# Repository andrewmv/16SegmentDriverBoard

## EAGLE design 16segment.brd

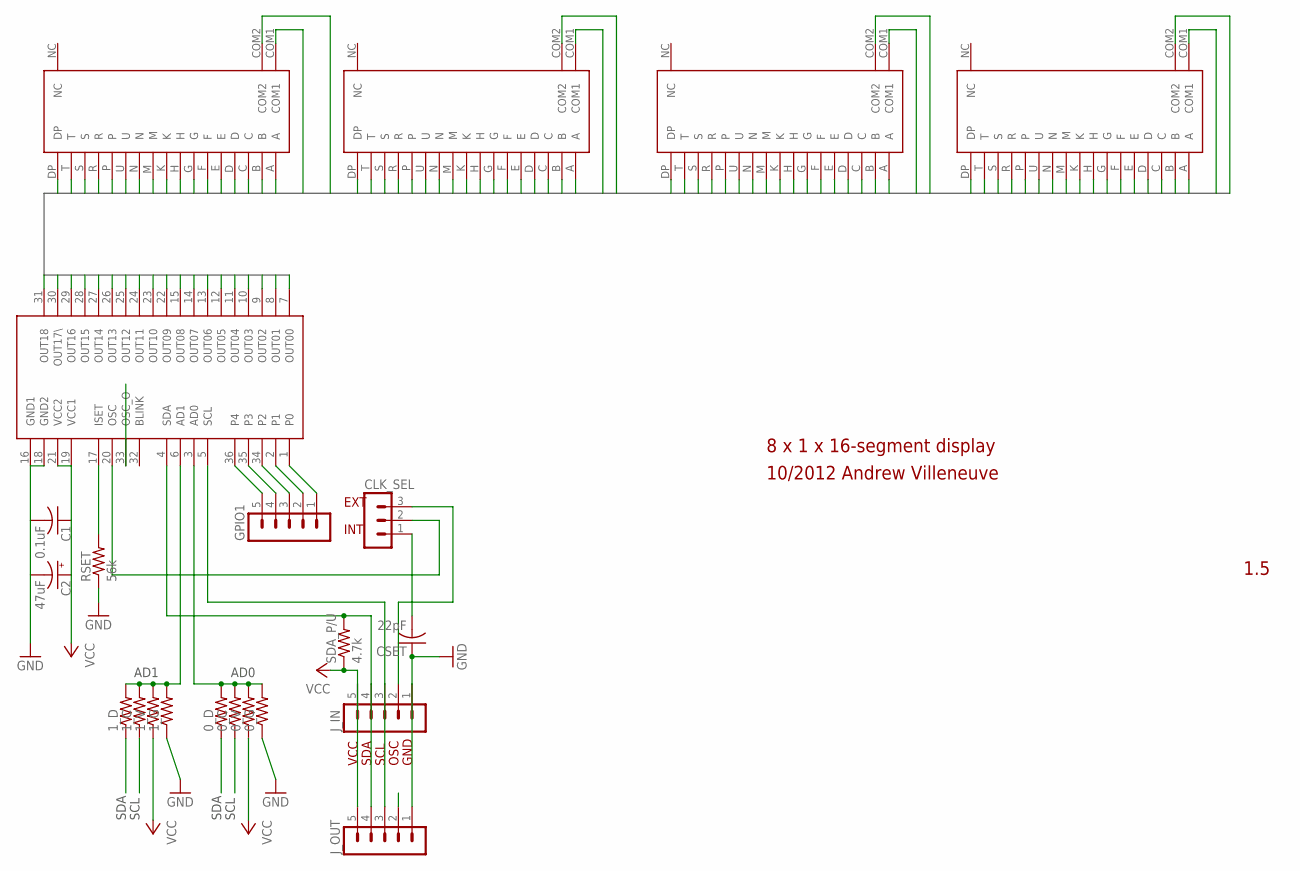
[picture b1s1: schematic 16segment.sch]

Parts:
0_C, 0_D, 0_G, 0_V, 1_C, 1_D, 1_G, 1_V: R-US_R0805; R0805
C1: 0.1uF; C0805
C2: 47uF; E2,5-6
CLK_SEL: MA03-1
CSET: 22pF; C0805
DIGIT0,1, DIGIT2,3, DIGIT4,5, DIGIT6,7: LTP-4323JD
GPIO1: MA05-1
IC1: MAX6955; SSOP36
J_IN: MA05-1
J_OUT: MA05-1
RSET: 56k; R0805
SDA_P/U: 4.7k; R0805

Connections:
AD0: 0_C.2, 0_D.2, 0_G.2, 0_V.2, IC1.3 (AD0)
AD1: 1_C.2, 1_D.2, 1_G.2, 1_V.2, IC1.6 (AD1)
EXT_OSC_IN: CLK_SEL.3, J_IN.2
GND: 0_G.1, 1_G.1, C1.2, C2.-, CSET.1, IC1.16 (GND1), IC1.18 (GND2), J_IN.1, J_OUT.1, RSET.1
GPIO_0: GPIO1.1, IC1.1 (P0)
GPIO_1: GPIO1.2, IC1.2 (P1)
GPIO_2: GPIO1.3, IC1.34 (P2)
GPIO_3: GPIO1.4, IC1.35 (P3)
GPIO_4: GPIO1.5, IC1.36 (P4)
IC1_OSC: CLK_SEL.2, IC1.20 (OSC)
INT_OSC: CLK_SEL.1, CSET.2
ISET: IC1.17 (ISET), RSET.2
OSC_O: IC1.33 (OSC_O), J_OUT.2
OUT0: DIGIT0,1.COM1, DIGIT2,3.A, DIGIT4,5.A, DIGIT6,7.A, IC1.7 (OUT00)
OUT1: DIGIT0,1.COM2, DIGIT2,3.B, DIGIT4,5.B, DIGIT6,7.B, IC1.8 (OUT01)
OUT2: DIGIT0,1.A, DIGIT2,3.COM1, DIGIT4,5.C, DIGIT6,7.C, IC1.9 (OUT02)
OUT3: DIGIT0,1.B, DIGIT2,3.COM2, DIGIT4,5.D, DIGIT6,7.D, IC1.10 (OUT03)
OUT4: DIGIT0,1.C, DIGIT2,3.C, DIGIT4,5.COM1, DIGIT6,7.E, IC1.11 (OUT04)
OUT5: DIGIT0,1.D, DIGIT2,3.D, DIGIT4,5.COM2, DIGIT6,7.F, IC1.12 (OUT05)
OUT6: DIGIT0,1.E, DIGIT2,3.E, DIGIT4,5.E, DIGIT6,7.COM1, IC1.13 (OUT06)
OUT7: DIGIT0,1.F, DIGIT2,3.F, DIGIT4,5.F, DIGIT6,7.COM2, IC1.14 (OUT07)
OUT8: DIGIT0,1.G, DIGIT2,3.G, DIGIT4,5.G, DIGIT6,7.G, IC1.15 (OUT08)
OUT9: DIGIT0,1.H, DIGIT2,3.H, DIGIT4,5.H, DIGIT6,7.H, IC1.22 (OUT09)
OUT10: DIGIT0,1.U, DIGIT2,3.U, DIGIT4,5.U, DIGIT6,7.U, IC1.23 (OUT10)
OUT11: DIGIT0,1.P, DIGIT2,3.P, DIGIT4,5.P, DIGIT6,7.P, IC1.24 (OUT11)
OUT12: DIGIT0,1.K, DIGIT2,3.K, DIGIT4,5.K, DIGIT6,7.K, IC1.25 (OUT12)
OUT13: DIGIT0,1.M, DIGIT2,3.M, DIGIT4,5.M, DIGIT6,7.M, IC1.26 (OUT13)
OUT14: DIGIT0,1.N, DIGIT2,3.N, DIGIT4,5.N, DIGIT6,7.N, IC1.27 (OUT14)
OUT15: DIGIT0,1.R, DIGIT2,3.R, DIGIT4,5.R, DIGIT6,7.R, IC1.28 (OUT15)
OUT16: DIGIT0,1.S, DIGIT2,3.S, DIGIT4,5.S, DIGIT6,7.S, IC1.29 (OUT16)
OUT17: DIGIT0,1.T, DIGIT2,3.T, DIGIT4,5.T, DIGIT6,7.T, IC1.30 (OUT17\)
OUT18: DIGIT0,1.DP, DIGIT2,3.DP, DIGIT4,5.DP, DIGIT6,7.DP, IC1.31 (OUT18)
SCL: 0_C.1, 1_C.1, IC1.5 (SCL), J_IN.3, J_OUT.3
SDA: IC1.4 (SDA), J_IN.4, J_OUT.4, SDA_P/U.2
SDA_0: 0_D.1, 1_D.1
VCC: 0_V.1, 1_V.1, C1.1, C2.+, IC1.19 (VCC1), IC1.21 (VCC2), J_IN.5, J_OUT.5, SDA_P/U.1

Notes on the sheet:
8 x 1 x 16-segment display
1.5
10/2012 Andrew Villeneuve
VCC
SDA
SCL
OSC
GND
INT
EXT
AD0
AD1

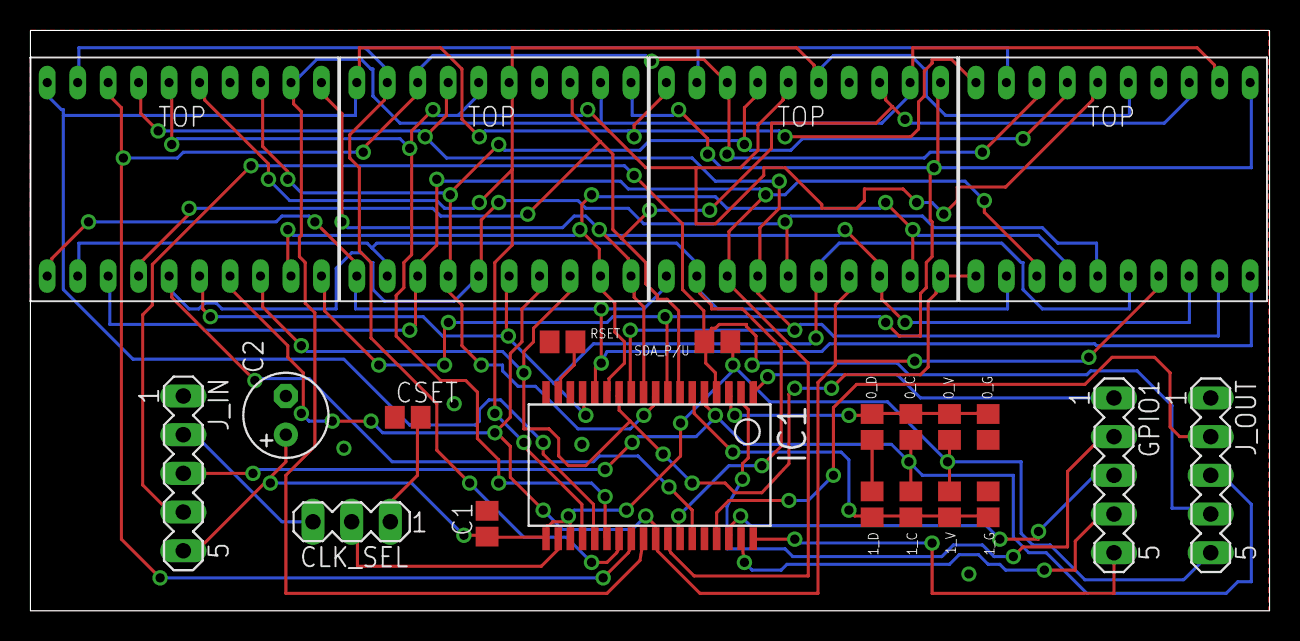
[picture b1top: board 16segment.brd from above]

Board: 2 copper layers, 81.3 x 38.1 mm, 22 parts (0 on the bottom side), 36 nets.

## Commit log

2016-11-03 :tada: Added .gitattributes & .gitignore files
